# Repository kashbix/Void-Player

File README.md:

# Void Player (Beta)

> **Status: Beta Release** \> Void Player is currently in its beta stage. While the core state-machine architecture, VLC playback engine, web dashboard, and headless integrations are stable, users may encounter edge cases depending on their specific hardware, rogue Bluetooth peripherals, or unsupported USB DACs. Bug reports and contributions are highly encouraged.

Void Player is a lightweight, high-performance headless audio engine designed specifically for the Raspberry Pi. Built entirely in Python, it bypasses standard desktop environments to deliver a pure, physical-button-driven music experience with a dynamic OLED interface, paired with a sleek, localized web dashboard for telemetry and hardware management.

At its core, Void Player utilizes a decoupled, non-blocking state-machine architecture. It handles hardware interrupts, dynamic audio routing, multithreaded display rendering, and SQLite telemetry without relying on standard `time.sleep()` UI loops, preventing thread starvation and ensuring a highly responsive tactile experience.

## Core Features

* **Local Web Dashboard & Hardware Sync:** A built-in FastAPI web server provides a sleek, bento-box style interface to control the physical hardware over your local network. Adjust boot volume, auto-play behavior, and OLED sleep timers, with changes syncing instantly to the hardware via internal JSON pipelines.
* **Granular Telemetry Engine:** A lightweight SQLite database tracks your top tracks, artists, genres, and listening habits locally. It calculates exactly how long you listen to a track versus skipping it. No cloud tracking, no subscriptions.
* **Decoupled State-Machine Architecture:** Uses a centralized event queue and an active button manager (`btn_mgr`) to safely bind and unbind GPIO interrupts across different menu states.
* **OLED Burn-In Protection:** Features a configurable sleep timer that actively monitors playback states. The screen gracefully blacks out when idle and features "Wake on Interaction" logic to prevent accidental skips when waking the display.
* **Headless Network & Power Management:** Includes a full physical power menu for safe reboots/shutdowns. The web dashboard also features a secure Wi-Fi configuration portal, allowing you to move the Pi to new networks without ever opening an SSH terminal.
* **VLC-Powered Playback Engine:** Supports FLAC, WAV, and MP3 formats with dynamic ID3 tag extraction via `tinytag`. Includes an isolated background thread for seamlessly wrapping long track titles and rendering playback states smoothly.

## Gallery

### Software Interface

* **The Web Dashboard**:   
* **File Transfer**: Drag-and-drop your audio files directly to the Pi's local storage.   
* **Device Management**: Restart, reboot, configure network settings, and update player preferences. 

### Hardware Prototype

* **Current Setup**: Currently running on a breadboard. Future plans include a custom PCB and a 3D-printed enclosure. 
* **Main Menu**: The physical `luma.oled` interface.  
* **Now Playing**: Features smooth scrolling text for long track names so nothing is cut off.  

## Hardware Requirements

* **SBC:** Raspberry Pi (Zero 2 W, 3, or 4 recommended for optimal VLC and PipeWire performance)
* **Display:** 128x64 I2C OLED Display (e.g., SSD1306)
* **Input:** 6x Tactile Push Buttons
* **Audio Output:** USB DAC (recommended for high-fidelity output) or a paired Bluetooth device.

## Hardware Setup & Wiring

Void Player relies on the Raspberry Pi's internal pull-up resistors. Each tactile button must be wired directly between its designated GPIO pin and any available Ground (GND) pin on the Pi. No external pull-up or pull-down resistors are required.

### GPIO Button Configuration

* **Menu / Back:** GPIO 24
* **Center / Select:** GPIO 18
* **Next Track / Down:** GPIO 22
* **Previous Track / Up:** GPIO 27
* **Volume Up:** GPIO 17
* **Volume Down:** GPIO 23

### OLED Display (I2C)

The SSD1306 display connects via the standard hardware I2C pins:

* **VCC:** 3.3V (Pin 1)
* **GND:** Ground (Pin 6 or Pin 9)
* **SDA:** GPIO 2 (Pin 3)
* **SCL:** GPIO 3 (Pin 5)

## Installation & Deployment

**1. Install System Dependencies** Ensure your Raspberry Pi has the following Linux backend utilities installed:

```bash
sudo apt-get update
sudo apt-get install vlc pulseaudio-utils pulseaudio-module-bluetooth bluez

# pillow dependencies
sudo apt-get install libfreetype6-dev libjpeg-dev zlib1g-dev python3-lgpio liblgpio-dev swig gcc
```

**2. Clone the Repository**

```bash
git clone https://github.com/kashbix/void-player.git
cd void-player

````

**3. Setup Python Environment** Create a virtual environment and install the required Python libraries:

```bash
python3 -m venv --system-site-packages .venv
source .venv/bin/activate
pip install -r requirements.txt
````

**4. Prepare the Music Directory** By default, the player scans for media in `/home/$USER/Music`. Ensure your FLAC, WAV, or MP3 files are placed in this directory, or upload them directly via the Web Dashboard. *(Optional: The UI uses `DejaVuSans-Bold.ttf`. If unavailable, `configs.py` falls back to the default Pillow font).*

**5. enable i2c in raspi-config**

```bash
sudo raspi-config
```

Arrow down to `interface options > I2C > Enable`

reboot at the popup, or later if you're already planning on it

**6. Ensure your user is in the proper groups**

```bash
sudo usermod -a -G gpio,i2c $USER
```

**7. Run the Application** Start the core hardware engine and web dashboard by executing the main script:

```bash
python3 main.py
```

### Accessing the Dashboard

Navigate to `http://<YOUR_PI_IP>:8000` on any device connected to the same local network.

> **Note:** If you don't know your Raspberry Pi's IP address, you can find it by checking your router's admin dashboard (under Network \> DHCP Server \> Client List), looking at the physical OLED screen via the "File Share" menu, or by running `hostname -I` directly on the Pi using a monitor.

*Deployment Note: For a true headless appliance experience, it is highly recommended to configure your script to run as a `systemd` background service on boot.*

## PCB manufacturing

If you'd like to export the board manually from the KiCad project, you can follow the written guide for your overseas manufacturer of choice. In hardware/Void_Player/GRBRs/single.zip, there is a
pre-generated JLCPCB-compliant .zip file ready to be uploaded at [jlcpcb.com](https://cart.jlcpcb.com/quote?stencilLayer=2&stencilWidth=100&stencilLength=100&stencilCounts=5&plateType=1&spm=Jlcpcb.Homepage.1010)

## License

This project is open-source and available under the MIT License. See the LICENSE file for further details.

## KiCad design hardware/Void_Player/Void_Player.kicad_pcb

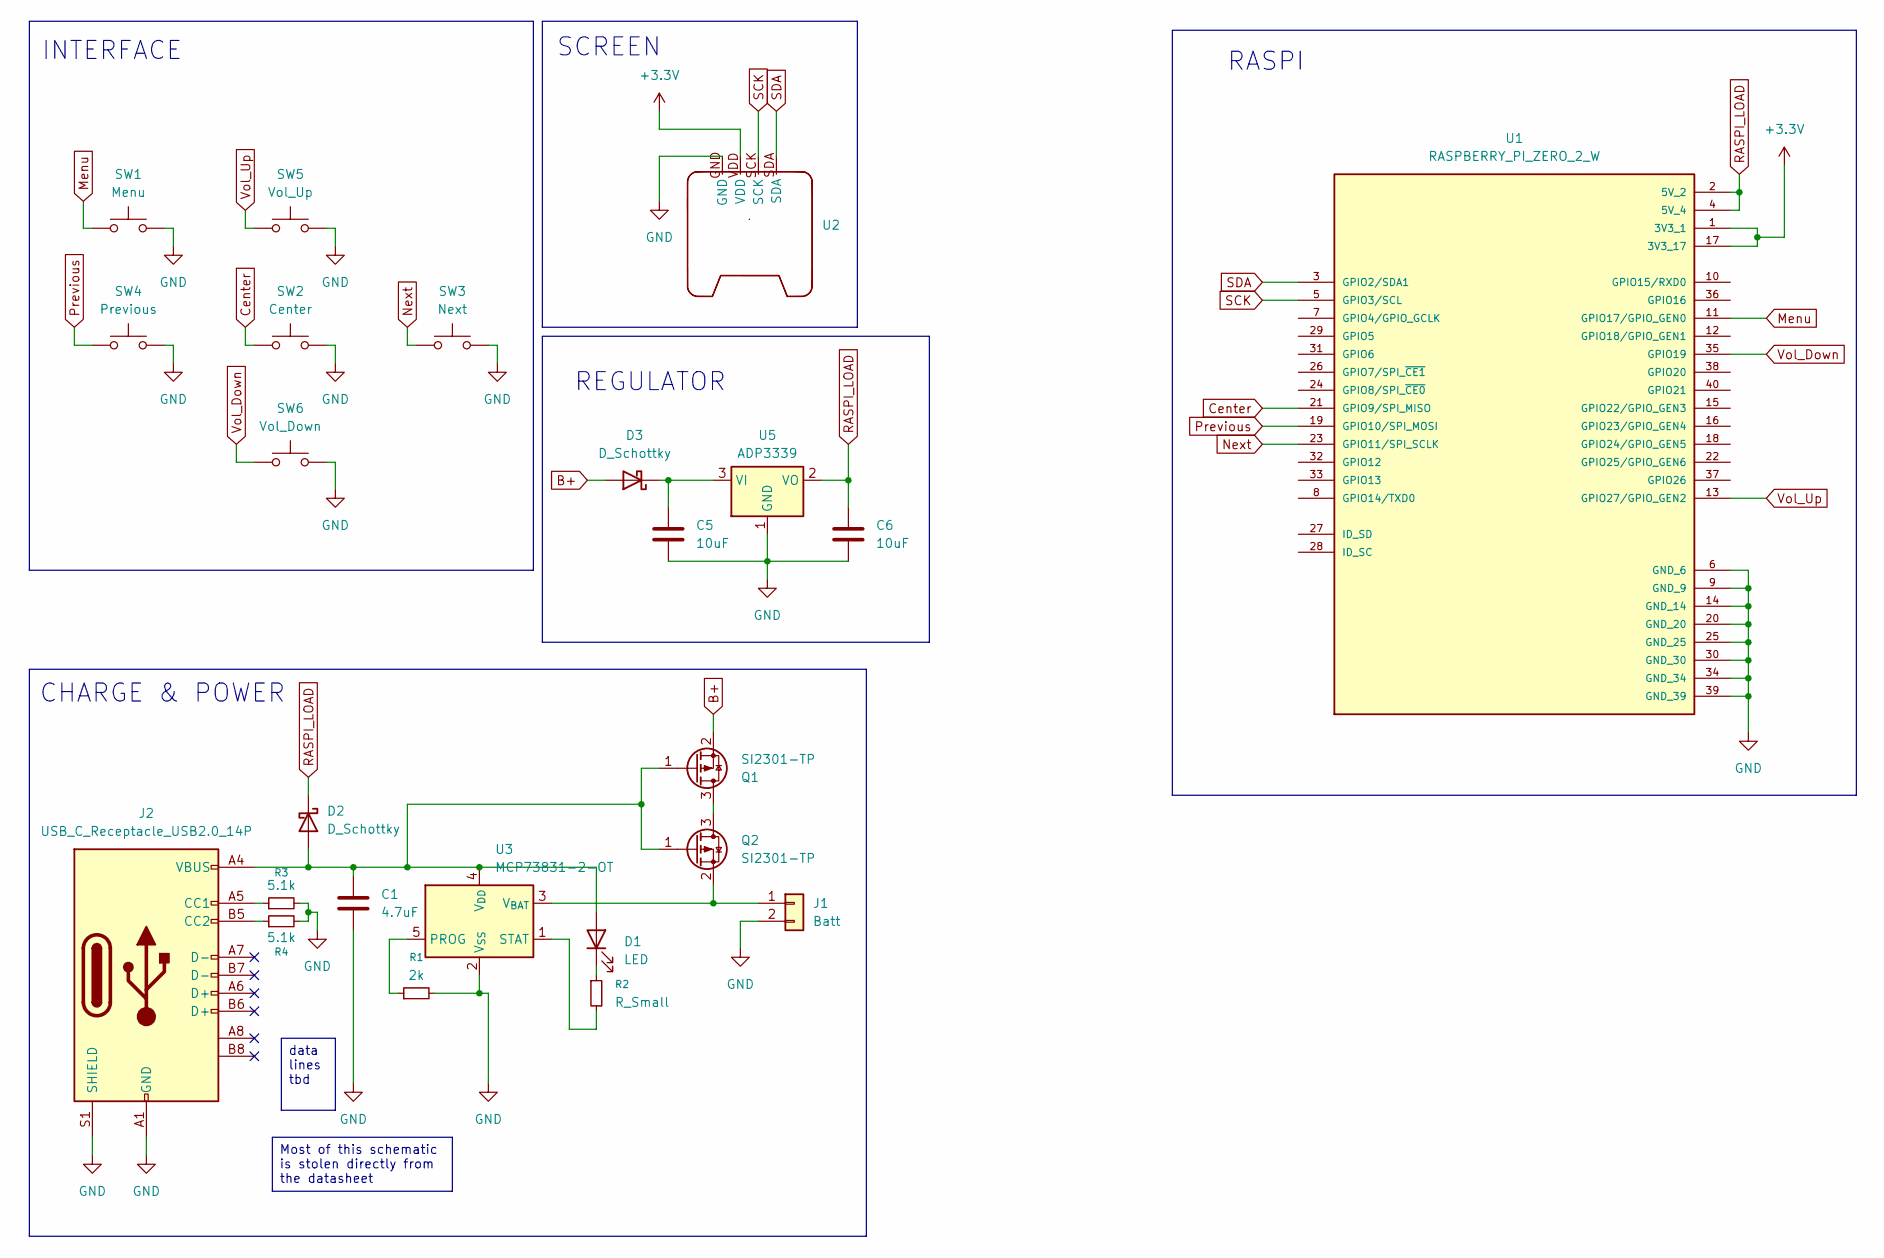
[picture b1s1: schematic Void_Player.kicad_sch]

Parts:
C1: 4.7uF; C_1206_3216Metric
C5, C6: 10uF; C_1206_3216Metric
D1: LED; D_1206_3216Metric
D2, D3: D_Schottky; D_1206_3216Metric
J1: Batt; JST_PH_S2B-PH-SM4-TB_1x02-1MP_P2.00mm_Horizontal
J2: USB_C_Receptacle_USB2.0_14P; USB_C_Receptacle_GCT_USB4110
Q1, Q2: SI2301-TP; SOT-23
R1: 2k; R_1206_3216Metric
R2: R_Small; R_1206_3216Metric
R3, R4: 5.1k; R_1206_3216Metric
SW1: Menu; SW_PUSH_6mm
SW2: Center; SW_PUSH_6mm
SW3: Next; SW_PUSH_6mm
SW4: Previous; SW_PUSH_6mm
SW5: Vol_Up; SW_PUSH_6mm
SW6: Vol_Down; SW_PUSH_6mm
U1: RASPBERRY_PI_ZERO_2_W; Raspberry_Pi_Zero_Socketed_THT_FaceDown_MountingHoles; PARTREV April 2024
U2: SSD1306
U3: MCP73831-2-OT; SOT-23-5
U5: ADP3339; SOT-223-3_TabPin2

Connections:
+3.3V: U1.1 (3V3_1), U1.17 (3V3_17), U2.VDD
B+: D3.2 (A), Q1.2 (S)
Center: SW2.1, U1.21 (GPIO9/SPI_MISO)
GND: C1.2, C5.2, C6.2, J1.2, J2.A1 (GND), J2.A12 (GND), J2.B1 (GND), J2.B12 (GND), J2.S1 (SHIELD), R1.2, R3.2, R4.2, SW1.2, SW2.2, SW3.2, SW4.2, SW5.2, SW6.2, U1.6 (GND_6), U1.9 (GND_9), U1.14 (GND_14), U1.20 (GND_20), U1.25 (GND_25), U1.30 (GND_30), U1.34 (GND_34), U1.39 (GND_39), U2.GND, U3.2 (V_{SS}), U5.1 (GND)
Menu: SW1.1, U1.11 (GPIO17/GPIO_GEN0)
unnamed: C1.1, D1.2 (A), D2.2 (A), J2.A4 (VBUS), J2.A9 (VBUS), J2.B4 (VBUS), J2.B9 (VBUS), Q1.1 (G), Q2.1 (G), U3.4 (V_{DD})
unnamed: D1.1 (K), R2.1
unnamed: C5.1, D3.1 (K), U5.3 (VI)
unnamed: J1.1, Q2.2 (S), U3.3 (V_{BAT})
unnamed: J2.A5 (CC1), R3.1
unnamed: J2.B5 (CC2), R4.1
unnamed: Q1.3 (D), Q2.3 (D)
unnamed: R1.1, U3.5 (PROG)
unnamed: R2.2, U3.1 (STAT)
Next: SW3.1, U1.23 (GPIO11/SPI_SCLK)
Previous: SW4.1, U1.19 (GPIO10/SPI_MOSI)
RASPI_LOAD: C6.1, D2.1 (K), U1.2 (5V_2), U1.4 (5V_4), U5.2 (VO)
SCK: U1.5 (GPIO3/SCL), U2.SCK
SDA: U1.3 (GPIO2/SDA1), U2.SDA
Vol_Down: SW6.1, U1.35 (GPIO19)
Vol_Up: SW5.1, U1.13 (GPIO27/GPIO_GEN2)

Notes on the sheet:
INTERFACE
REGULATOR
RASPI
CHARGE & POWER
SCREEN
Most of this schematic is stolen directly from the datasheet
data lines tbd

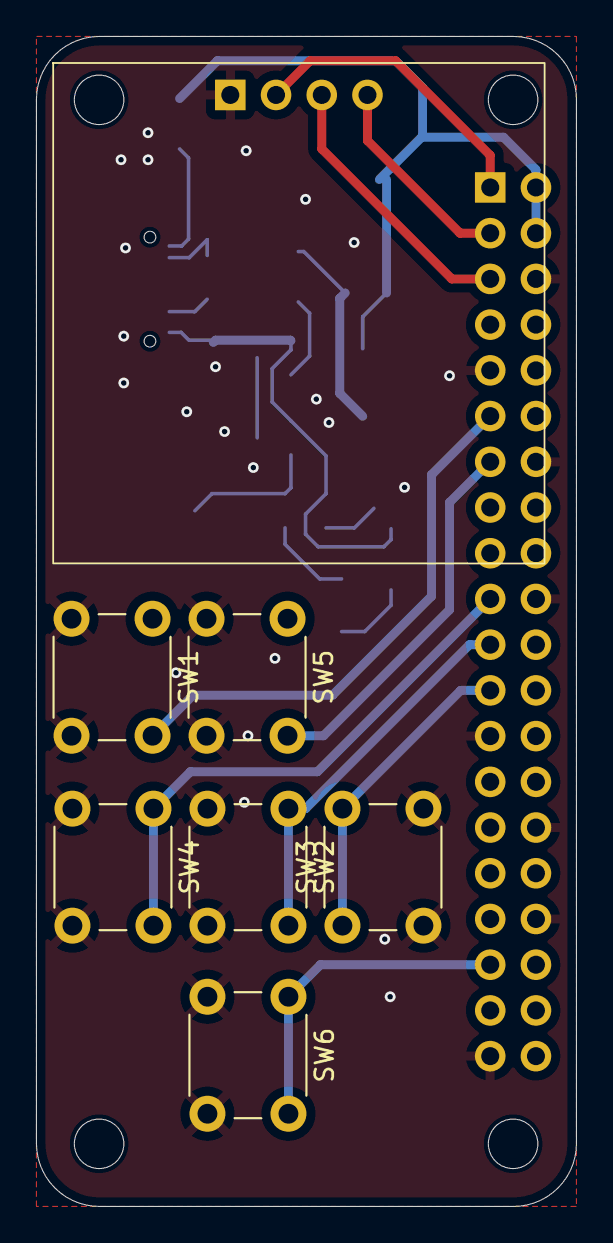
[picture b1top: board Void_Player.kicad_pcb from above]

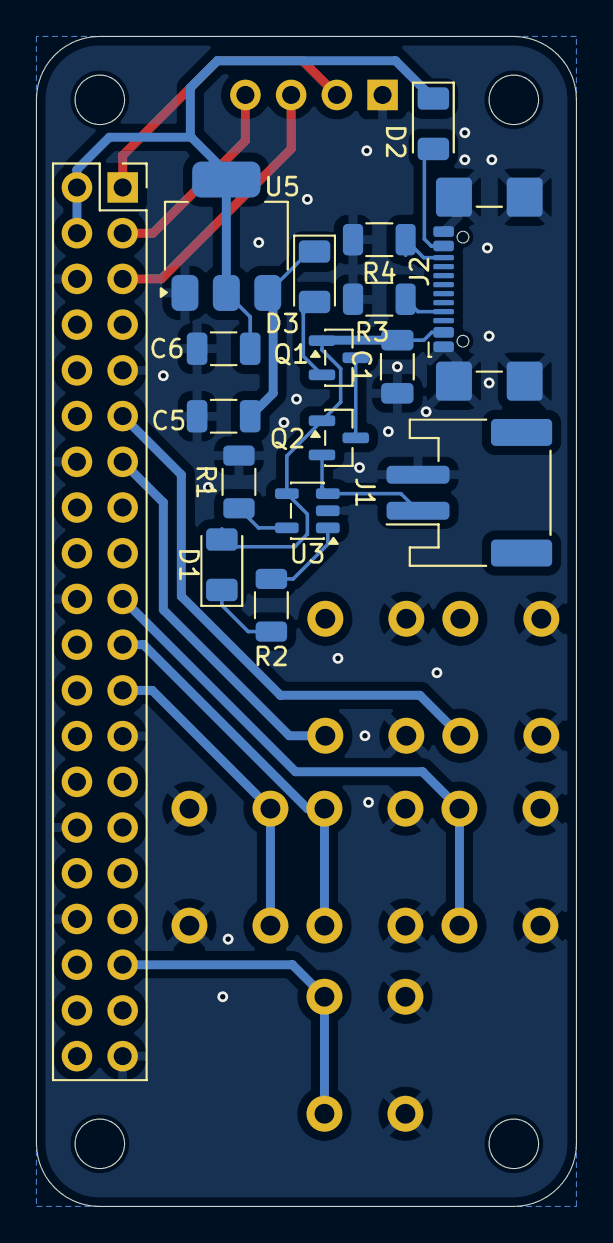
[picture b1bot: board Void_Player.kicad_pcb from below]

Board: 2 copper layers, 30.0 x 65.0 mm, 24 parts (17 on the bottom side), 21 nets.

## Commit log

2026-03-01 Initial commit: Core architecture
2026-03-01 Create LICENSE
2026-03-22 Web Dashboard and Bug fxies
2026-03-25 added pcb with lipo circuitry
2026-03-26 added PCB screenshot and JLC-compliant GRBRs
2026-04-09 added some README instructions after my install troubles
